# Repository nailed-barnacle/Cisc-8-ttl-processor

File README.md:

# Cisc-8-ttl-processor
A cut-down version of the 8080 processor using HCTTL and including a discrete ALU and instruction decoder

This is an attempt to replicate most of the functionality of the 1970s Intel 8080 processor using contemporary
HCTTL surface mount components.

By implementing most - though by no means all - of the instructions of the 8080 it allows the use of existing 
toolchains to generate code for the device both for the hardware implementation and the associated simulation.

The programmer's model is the same as the original 8080 - the following instructions are implemented (refer to an 8080 manual for details):

mov add adc sub sbb ana xra ora adi aci sui sbi ani xri ori sphl lxi dad lda sta mvi push pop jmp jnz jz jnc jc call ret 

All other instructions are unimplemented. There are minor changes regarding push/pull, in that push writes to the stack pointer address and then decrements it (and pull increments it and then reads) while the 8080 decrements before pushing. Additionally, it is not possible to mvi to m (hl).

A single non-maskable interrupt is provided, with a hard call to 0x0008 at the end of the current instruction (reset starts at 0x0000)

A two-internal bus model is used, which approximately doubles the speed (in clock cycles) of the original 8080. The longest instruction is the call, which requires 7 cycles.

Provided here are Kicad files for the schematics, Bill of Materials, and the final 200x300mm PCB. The normal
processor interface - data and address bus, power, clock etc are provided through a 40-pin header which would
attach to an adjacent board providing memory, serial port etc.

Recommended for assembling 8080 code in the browser: https://svofski.github.io/pretty-8080-assembler/

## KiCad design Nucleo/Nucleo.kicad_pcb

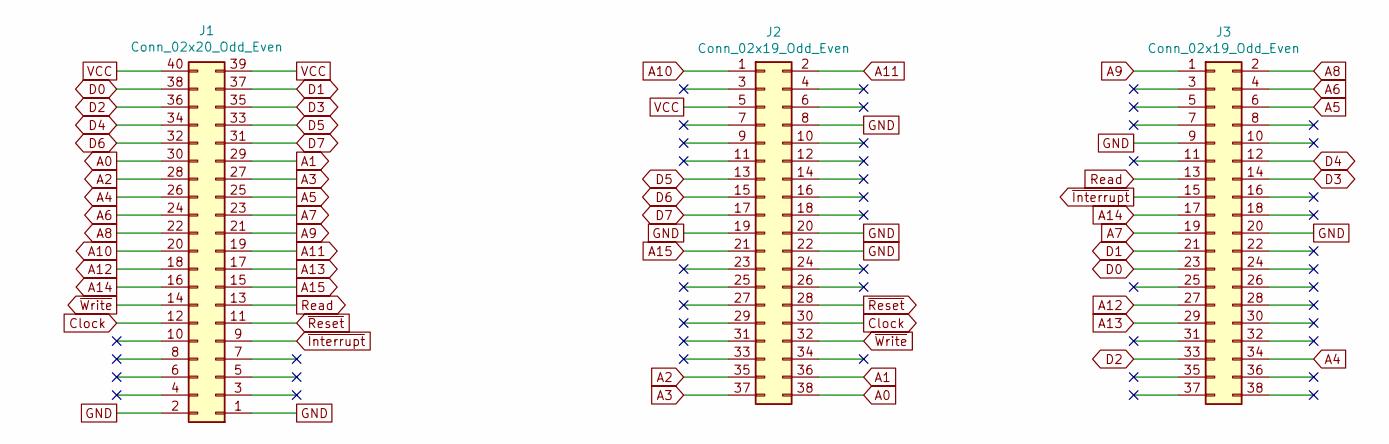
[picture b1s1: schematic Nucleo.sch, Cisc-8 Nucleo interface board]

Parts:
J1: Conn_02x20_Odd_Even; PinHeader_2x20_P2.54mm_Vertical_SMD
J2, J3: Conn_02x19_Odd_Even; PinHeader_2x19_P2.54mm_Vertical

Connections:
A0: J1.30, J2.38
A1: J1.29, J2.36
A2: J1.28, J2.35
A3: J1.27, J2.37
A4: J1.26, J3.34
A5: J1.25, J3.6
A6: J1.24, J3.4
A7: J1.23, J3.19
A8: J1.22, J3.2
A9: J1.21, J3.1
A10: J1.20, J2.1
A11: J1.19, J2.2
A12: J1.18, J3.27
A13: J1.17, J3.29
A14: J1.16, J3.17
A15: J1.15, J2.21
Clock: J1.12, J2.30
D0: J1.38, J3.23
D1: J1.37, J3.21
D2: J1.36, J3.33
D3: J1.35, J3.14
D4: J1.34, J3.12
D5: J1.33, J2.13
D6: J1.32, J2.15
D7: J1.31, J2.17
GND: J1.1, J1.2, J2.8, J2.19, J2.20, J2.22, J3.9, J3.20
Read: J1.13, J3.13
VCC: J1.39, J1.40, J2.5
~Interrupt: J1.9, J3.15
~Reset: J1.11, J2.28
~Write: J1.14, J2.32

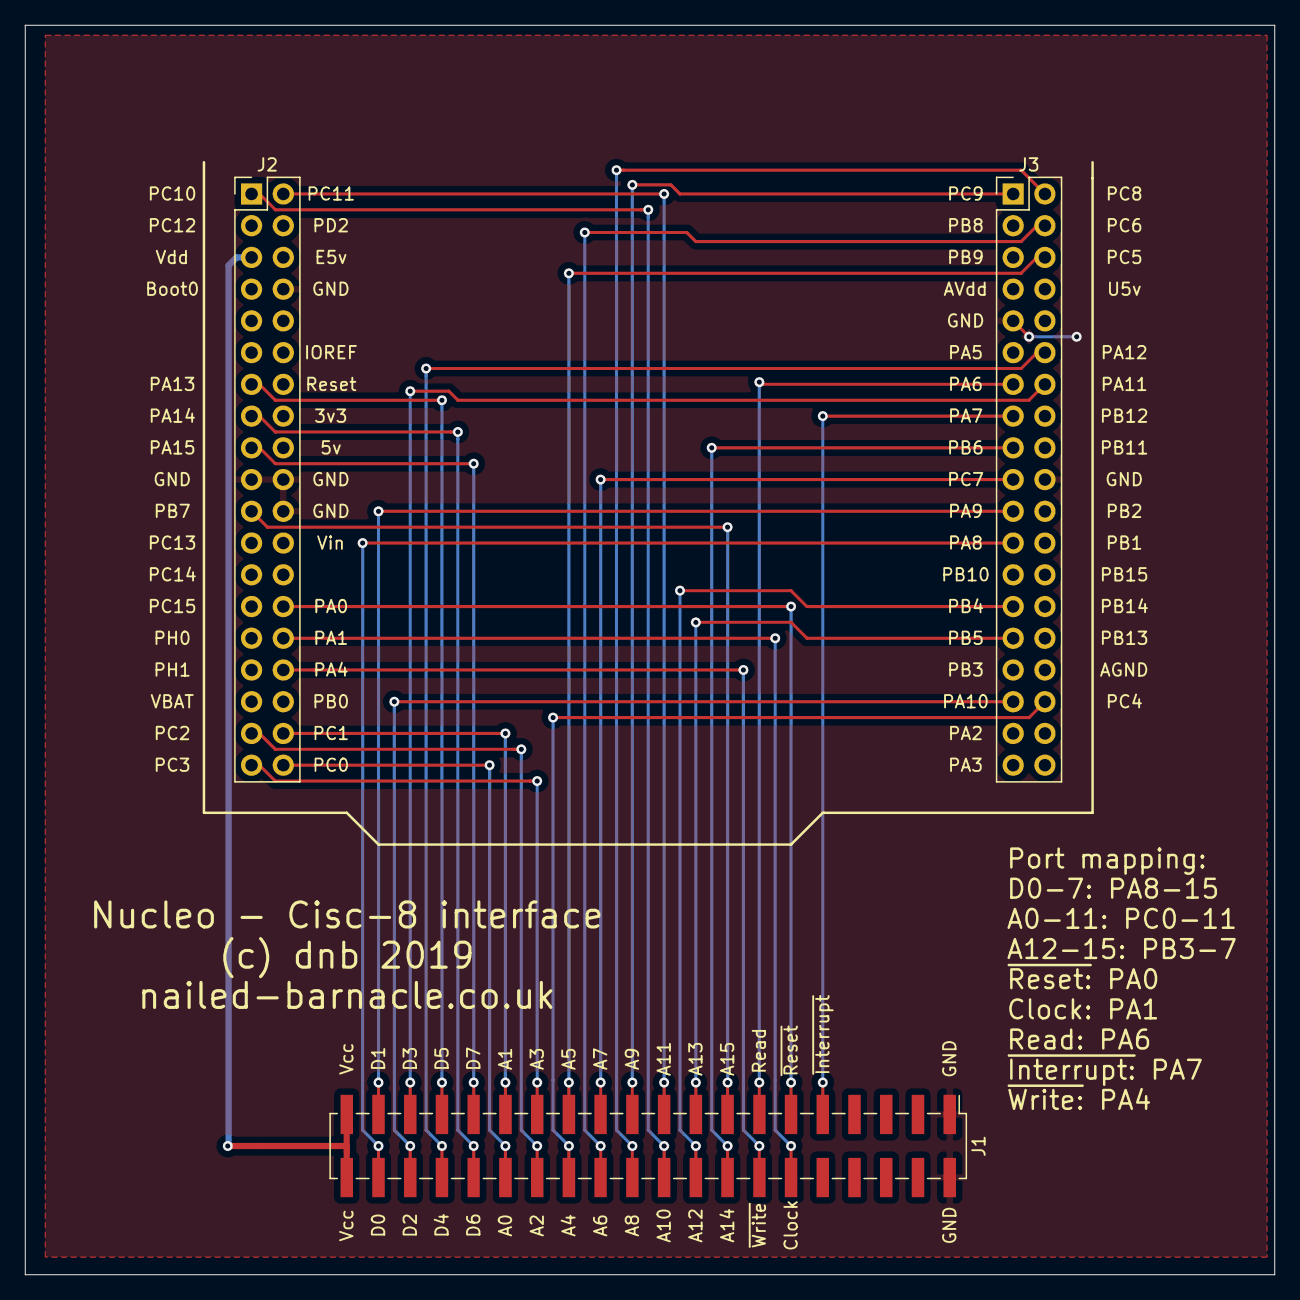
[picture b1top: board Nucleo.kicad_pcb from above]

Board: 2 copper layers, 100.0 x 100.0 mm, 3 parts (0 on the bottom side), 31 nets.

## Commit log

2019-07-22 Initial commit
    Hardware design including Kikad schematics, PCB layout, gerbers and BOM
2019-07-23 Create LICENSE
2019-07-23 Logisim simulation files added
    Logisim files - open cisc-8-2-ttl.circ to get a working system. Don't
    forget to write code...
2019-07-24 Update README.md
    Fixed date typo
2019-07-28 Added Nucleo interface board
    The Nucleo connects directly to the Cisc-8 and will emulate 16k of
    memory as well as providing clock, reset, and serial i/o capability.
2019-08-11 Minor changes to documentation
    Tidied up schematics, corrected a couple of errors in the instruction
    decoder, added pdf of complete schematics
